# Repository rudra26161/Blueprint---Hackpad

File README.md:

# Rudra's Hack Pad!

This is a custom hackpad made and designed by me featuring 15 keys and one rotary encoder with 2 led lights. 

---

##  Screenshots
### Final hackpad

### Overall Hackpad

### Schematic

### PCB Layout

### Case & Assembly

---

##  Bill of Materials (BOM)

- 1x XIAO RP2040 controller - [link](https://www.seeedstudio.com/XIAO-RP2040-v1-0-p-5026.html) - $3.99
- 15x Mx-switches - [link](https://www.aliexpress.us/item/3256806069646359.html?spm=a2g0o.productlist.main.3.1aaf3a606S7mA1&algo_pvid=4a72b84e-589c-4271-94cb-ea260cb23fb8&algo_exp_id=4a72b84e-589c-4271-94cb-ea260cb23fb8-2&pdp_ext_f=%7B%22order%22%3A%22976%22%2C%22eval%22%3A%221%22%2C%22fromPage%22%3A%22search%22%7D&pdp_npi=6%40dis%21USD%215.95%215.20%21%21%2141.12%2135.97%21%402101e80317697261566706594e0e14%2112000036489552472%21sea%21US%216344712987%21X%211%210%21n_tag%3A-29919%3Bd%3A10691efc%3Bm03_new_user%3A-29895%3BpisId%3A5000000198867400&curPageLogUid=UoXiemWT8jzM&utparam-url=scene%3Asearch%7Cquery_from%3A%7Cx_object_id%3A1005006255961111%7C_p_origin_prod%3A) - $8.27
- 16x 1N4148 diodes - [link](https://www.aliexpress.com/ssr/300000512/BundleDeals2?spm=a2g0o.productlist.main.2.4d602d8bmFbxwH&productIds=1005008631544226:12000046027852084&pha_manifest=ssr&_immersiveMode=true&disableNav=YES&sourceName=SEARCHProduct&utparam-url=scene%3Asearch%7Cquery_from%3A%7Cx_object_id%3A1005008631544226%7C_p_origin_prod%3A&pvid=1ff46287-debc-496d-9b9f-a2fdb9483380) - $1.39
- 1x Rotary encoder with switch - [link](https://www.aliexpress.us/item/3256807457768762.html?spm=a2g0o.productlist.main.6.148bHAkHHAkHEv&algo_pvid=8474a012-12a2-4d7e-a743-1c3f3dcf42fa&algo_exp_id=8474a012-12a2-4d7e-a743-1c3f3dcf42fa-5&pdp_ext_f=%7B%22order%22%3A%22698%22%2C%22eval%22%3A%221%22%2C%22fromPage%22%3A%22search%22%7D&pdp_npi=6%40dis%21USD%211.52%211.38%21%21%211.52%211.38%21%402101e80317697263568368265e0e3e%2112000041630839427%21sea%21US%216344712987%21X%211%210%21n_tag%3A-29919%3Bd%3A77ca77b6%3Bm03_new_user%3A-29895%3BpisId%3A5000000198867400&curPageLogUid=SymjeGT8HqoD&utparam-url=scene%3Asearch%7Cquery_from%3A%7Cx_object_id%3A1005007644083514%7C_p_origin_prod%3A) - $1.38
- 2x SK6812MINI RGB LED - [link](https://www.aliexpress.us/item/3256808122486614.html?spm=a2g0o.productlist.main.6.745atAhbtAhbWc&algo_pvid=21db06c4-b073-435f-bc92-19f7084d6967&algo_exp_id=21db06c4-b073-435f-bc92-19f7084d6967-5&pdp_ext_f=%7B%22order%22%3A%2248%22%2C%22eval%22%3A%221%22%2C%22fromPage%22%3A%22search%22%7D&pdp_npi=6%40dis%21USD%212.31%212.17%21%21%2115.97%2115.01%21%402101d49617697263946232720ec4e4%2112000044567528124%21sea%21US%216344712987%21X%211%210%21n_tag%3A-29919%3Bd%3A77ca77b6%3Bm03_new_user%3A-29895&curPageLogUid=tnzvZfAUcjjk&utparam-url=scene%3Asearch%7Cquery_from%3A%7Cx_object_id%3A1005008308801366%7C_p_origin_prod%3A) - $2.17
- 1x Pcb - no link - ~$5
- 1X 3d printed case - no link - free
- 4x Screws + standoffs for case assembly - no link - idk

---

##  Firmware
- Written in [KMK Firmware](https://github.com/rudra26161/Blueprint---Hackpad/blob/c94d1e2d607d7ab2b1c8bd9e36697b46c6f0982a/Firmware/kmk%20Hackpad)

## Other
pray for me that this works

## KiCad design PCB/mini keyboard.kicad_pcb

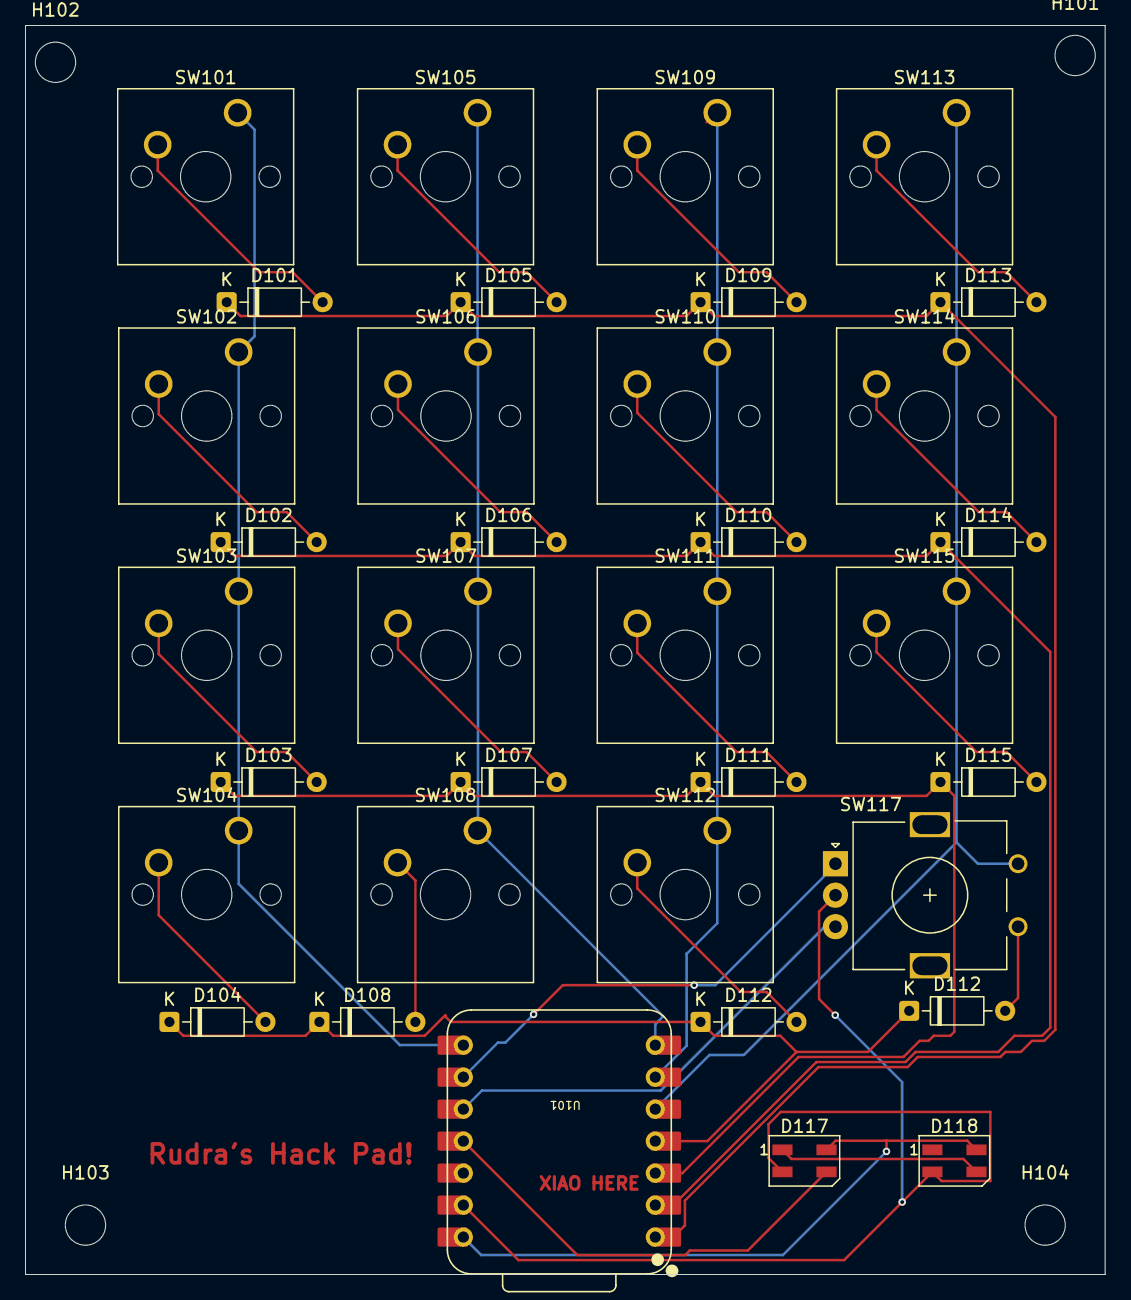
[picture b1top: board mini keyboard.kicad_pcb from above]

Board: 2 copper layers, 85.7 x 99.2 mm, 39 parts (0 on the bottom side), 29 nets.

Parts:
D101, D102, D103, D104, D105, D106, D107, D108, D109, D110, D111, D112, D112#2, D113, D114, D115: 1N4148; D_DO-35_SOD27_P7.62mm_Horizontal
D117, D118: SK6812MINI; LED_SK6812MINI_PLCC4_3.5x3.5mm_P1.75mm
H101, H102, H103, H104: MountingHole; MountingHole_3.2mm_M3
SW101, SW102, SW103, SW104, SW105, SW106, SW107, SW108, SW109, SW110, SW111, SW112, SW113, SW114, SW115: SW_Push; SW_Cherry_MX_1.00u_PCB
SW117: RotaryEncoder; RotaryEncoder_Alps_EC11E_Vertical_H20mm
U101: XIAO-RP2040-DIP

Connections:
+5V: D117.4 (VDD), D118.4 (VDD), U101.14 (VBUS)
GND: D117.2 (VSS), D118.2 (VSS), SW117.C, U101.13 (GND)
unnamed: D101.2 (A), SW101.2
unnamed: D101.1 (K), D105.1 (K), D109.1 (K), D113.1 (K), U101.1 (GPIO26/ADC0/A0)
unnamed: D102.2 (A), SW102.2
unnamed: D102.1 (K), D106.1 (K), D110.1 (K), D114.1 (K), U101.2 (GPIO27/ADC1/A1)
unnamed: D103.2 (A), SW103.2
unnamed: D103.1 (K), D107.1 (K), D111.1 (K), D115.1 (K), U101.3 (GPIO28/ADC2/A2)
unnamed: D104.2 (A), SW104.2
unnamed: D104.1 (K), D108.1 (K), D112.1 (K), D112#2.1 (K), U101.4 (GPIO29/ADC3/A3)
unnamed: D105.2 (A), SW105.2
unnamed: D106.2 (A), SW106.2
unnamed: D107.2 (A), SW107.2
unnamed: D108.2 (A), SW108.2
unnamed: D109.2 (A), SW109.2
unnamed: D110.2 (A), SW110.2
unnamed: D111.2 (A), SW111.2
unnamed: D112#2.2 (A), SW112.2
unnamed: D113.2 (A), SW113.2
unnamed: D114.2 (A), SW114.2
unnamed: D115.2 (A), SW115.2
unnamed: D117.3 (DIN), U101.11 (GPIO3/MOSI)
unnamed: D117.1 (DOUT), D118.3 (DIN)
unnamed: SW105.1, SW106.1, SW107.1, SW108.1, U101.7 (GPIO0/TX)
unnamed: SW101.1, SW102.1, SW103.1, SW104.1, U101.8 (GPIO1/RX)
unnamed: SW117.A, U101.9 (GPIO2/SCK)
unnamed: SW117.B, U101.10 (GPIO4/MISO)
unnamed: SW113.1, SW114.1, SW115.1, U101.5 (GPIO6/SDA)
unnamed: SW109.1, SW110.1, SW111.1, SW112.1, U101.6 (GPIO7/SCL)

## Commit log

2025-12-05 more files!
2025-12-05 firmware
2025-12-11 Revise README with project details and features
    Added detailed project information, features, and BOM.
2025-12-11 photos
2025-12-11 Fix screenshot link in README.md
    Updated the link for the Hackpad overview screenshot.
2025-12-11 Fix PCB screenshot link in README
2025-12-11 Add KMK keyboard firmware for custom keymap
2025-12-11 Update case screenshot and firmware link
    Updated screenshots and firmware link in README.
2025-12-11 Create PCB
2025-12-12 Update screenshot in README for final hackpad
2025-12-12 no more AI :)
    Updated README to improve clarity and organization of features and BOM.
2025-12-12 Add personal note in README
    Added a personal note to the README file.
2026-01-29 fixed BOM
